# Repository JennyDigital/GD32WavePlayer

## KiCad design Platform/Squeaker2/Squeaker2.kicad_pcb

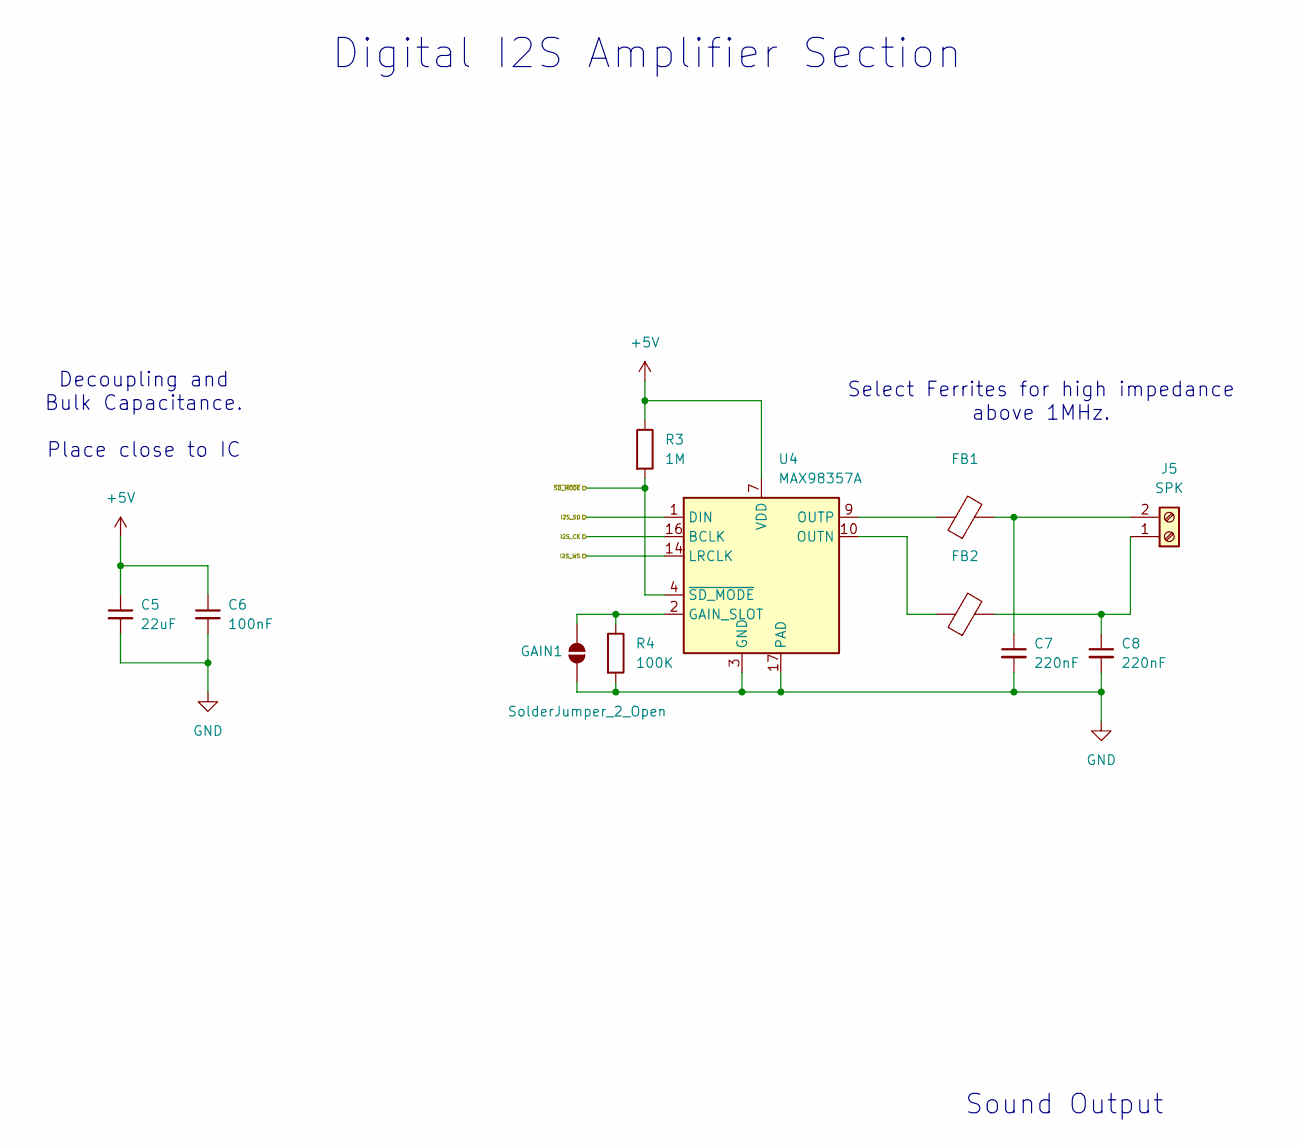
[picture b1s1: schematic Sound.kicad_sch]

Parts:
C5: 22uF; C_0603_1608Metric
C6: 100nF; C_0603_1608Metric
C7, C8: 220nF; C_0603_1608Metric
FB1, FB2: FerriteBead; L_0603_1608Metric
GAIN1: SolderJumper_2_Open; SolderJumper-2_P1.3mm_Open_RoundedPad1.0x1.5mm
J5: SPK; TerminalBlock_MetzConnect_Type073_RT02602HBLU_1x02_P5.08mm_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
R3: 1M; R_0603_1608Metric
R4: 100K; R_0603_1608Metric
U4: MAX98357A; TQFN-16-1EP_3x3mm_P0.5mm_EP1.23x1.23mm

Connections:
+5V: C5.1, C6.1, R3.1, U4.7 (VDD), U4.8 (VDD); also elsewhere on the board
/Processor/I2S_CK: U4.16 (BCLK); also elsewhere on the board
/Processor/I2S_SD: U4.1 (DIN); also elsewhere on the board
/Processor/I2S_WS: U4.14 (LRCLK); also elsewhere on the board
/Processor/~SD_MODE: R3.2, U4.4 (~SD_MODE); also elsewhere on the board
GND: C5.2, C6.2, C7.2, C8.2, GAIN1.1 (A), R4.2, U4.3 (GND), U4.11 (GND), U4.15 (GND), U4.17 (PAD); also elsewhere on the board
unnamed: GAIN1.2 (B), R4.1, U4.2 (GAIN_SLOT)
unnamed: C8.1, FB2.2, J5.1
unnamed: C7.1, FB1.2, J5.2
unnamed: FB2.1, U4.10 (OUTN)
unnamed: FB1.1, U4.9 (OUTP)

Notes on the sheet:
Sound Output
Select Ferrites for high impedance above 1MHz.
Digital I2S Amplifier Section
Decoupling and Bulk Capacitance. Place close to IC

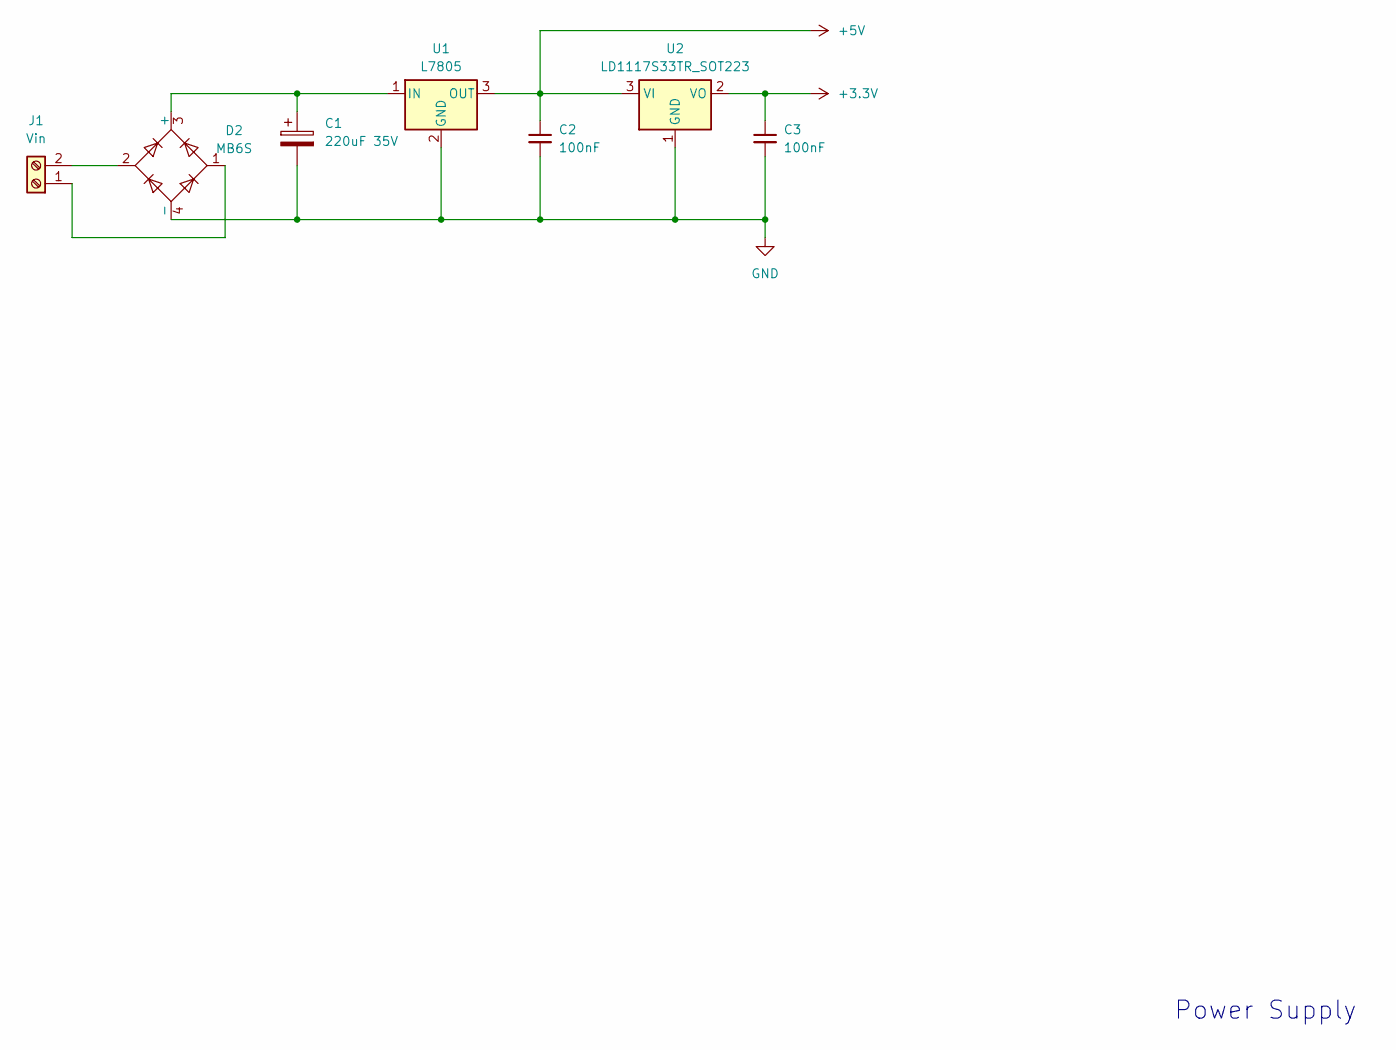
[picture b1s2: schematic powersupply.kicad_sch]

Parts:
C1: 220uF 35V; CP_Elec_8x10.5
C2, C3: 100nF; C_0603_1608Metric
D2: MB6S; TO-269AA
J1: Vin; TerminalBlock_MetzConnect_Type073_RT02602HBLU_1x02_P5.08mm_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
U1: L7805; TO-263-2
U2: LD1117S33TR_SOT223; SOT-223-3_TabPin2

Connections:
+3.3V: C3.1, U2.2 (VO); also elsewhere on the board
+5V: C2.1, U1.3 (OUT), U2.3 (VI); also elsewhere on the board
GND: C1.2, C2.2, C3.2, D2.4 (-), U1.2 (GND), U2.1 (GND); also elsewhere on the board
unnamed: C1.1, D2.3 (+), U1.1 (IN)
unnamed: D2.1, J1.1
unnamed: D2.2, J1.2

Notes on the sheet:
Power Supply

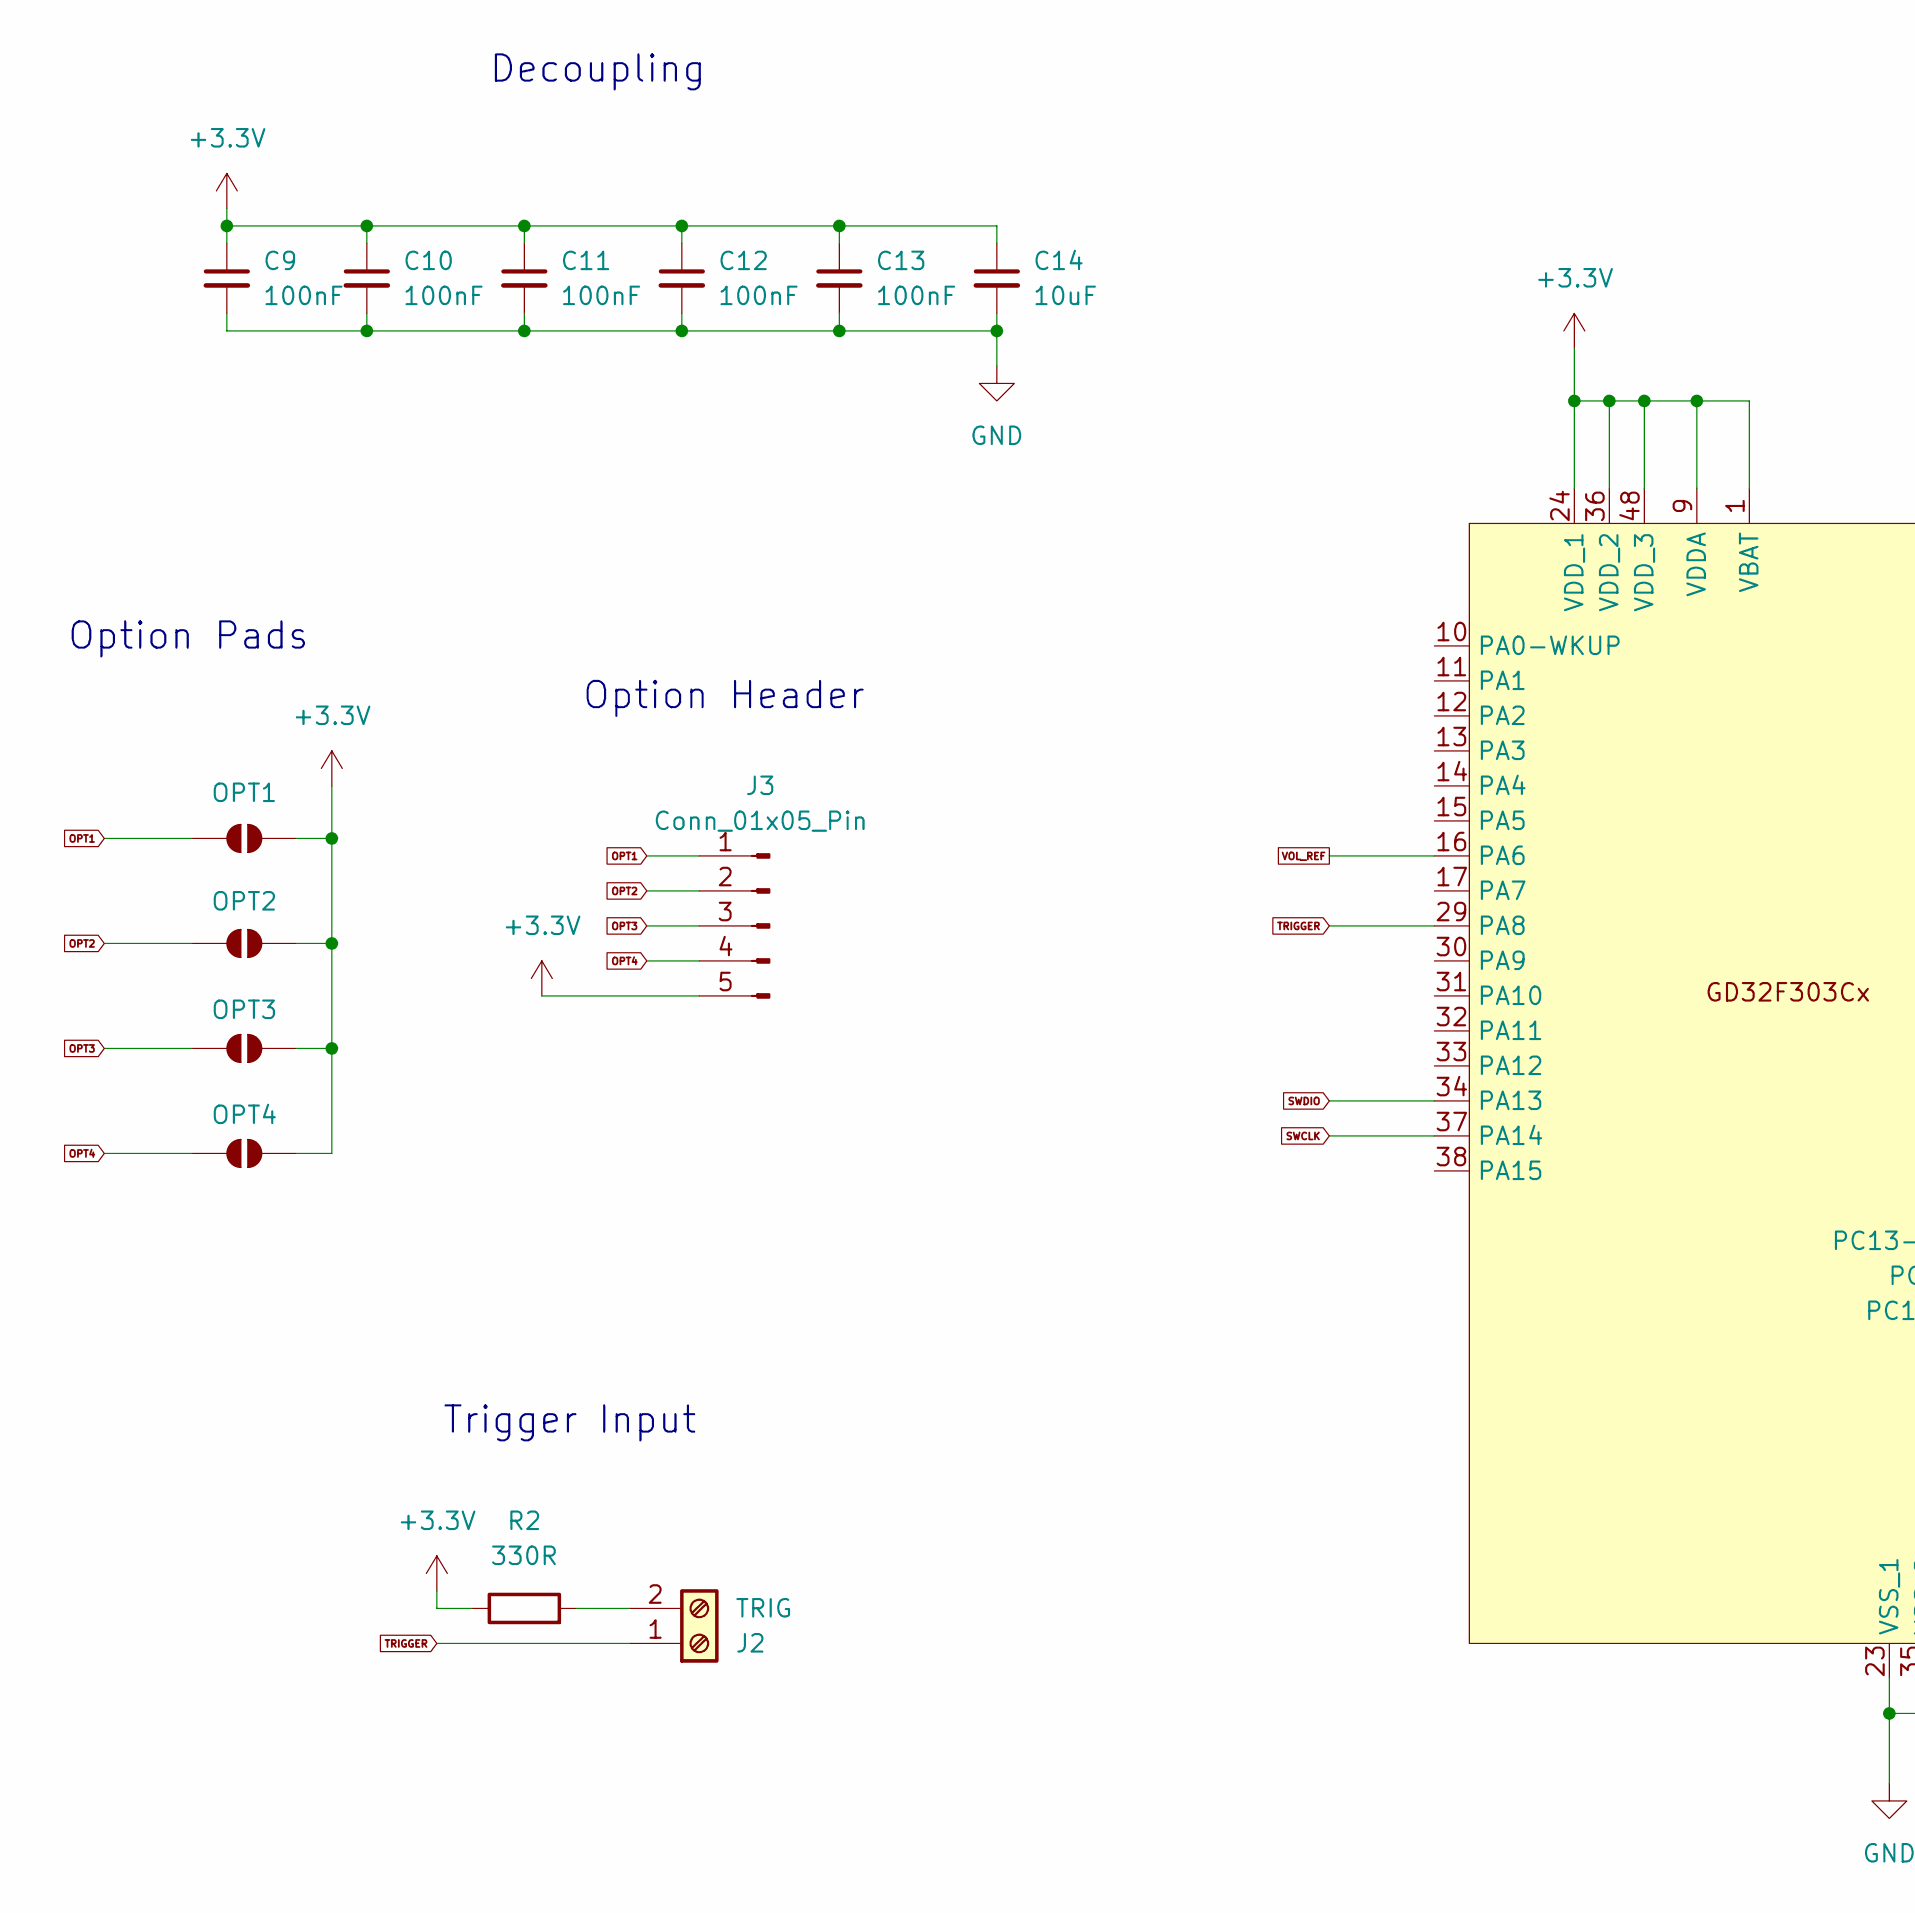
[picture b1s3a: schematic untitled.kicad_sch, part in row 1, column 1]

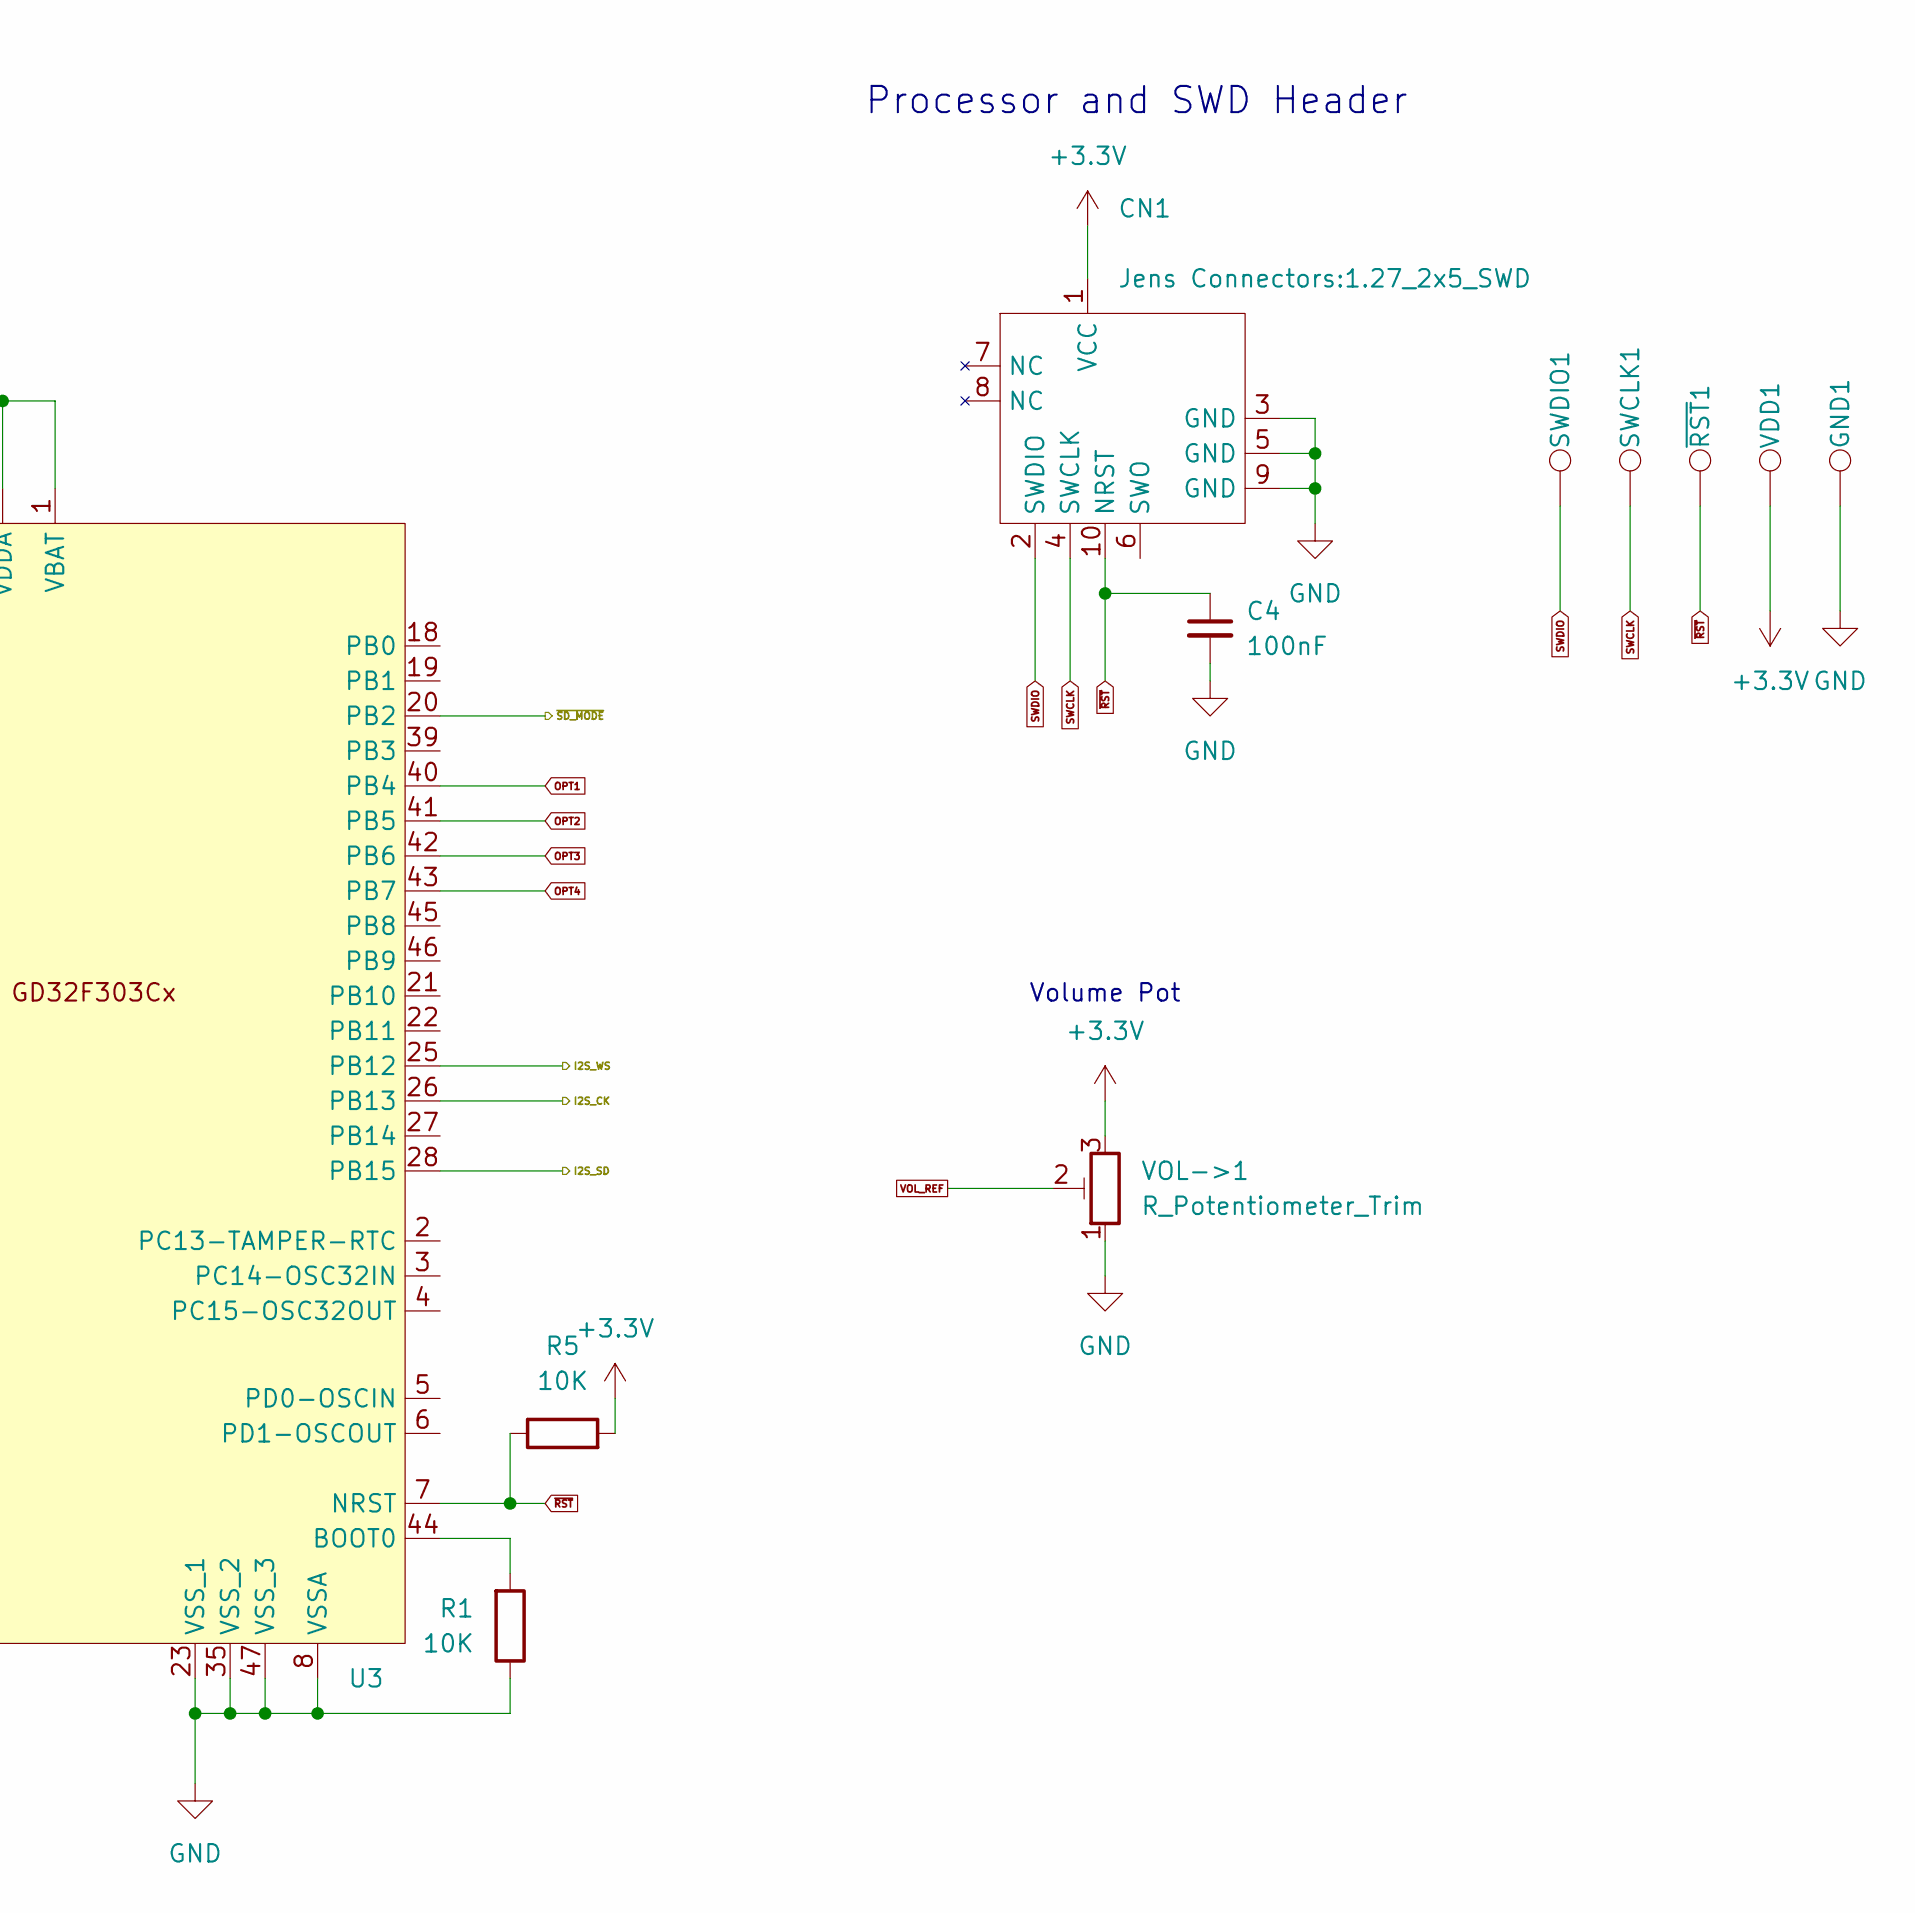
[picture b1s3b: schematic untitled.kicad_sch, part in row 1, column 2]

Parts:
C4, C9, C10, C11, C12, C13: 100nF; C_0603_1608Metric
C14: 10uF; C_0603_1608Metric
CN1: 1.27_2x5_SWD
GND1: TestPoint; TestPoint_Pad_D2.0mm
J2: TRIG; TerminalBlock_MetzConnect_Type073_RT02602HBLU_1x02_P5.08mm_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
J3: Conn_01x05_Pin; PinHeader_1x05_P2.54mm_Vertical
OPT1, OPT2, OPT3, OPT4: SolderJumper-2_P1.3mm_Open_RoundedPad1.0x1.5mm
R1, R5: 10K; R_0603_1608Metric
R2: 330R; R_0603_1608Metric
SWCLK1: TestPoint; TestPoint_Pad_D2.0mm
SWDIO1: TestPoint; TestPoint_Pad_D2.0mm
U3: TQFP-48_7x7mm_P0.5mm
VDD1: TestPoint; TestPoint_Pad_D2.0mm
VOL->1: R_Potentiometer_Trim; BOURNS-3362P_pot
~{RST}1: TestPoint; TestPoint_Pad_D2.0mm

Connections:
+3.3V: C9.1, C10.1, C11.1, C12.1, C13.1, C14.1, CN1.1 (VCC), J3.5, OPT1.2 (B), OPT2.2 (B), OPT3.2 (B), OPT4.2 (B), R2.1, R5.2, U3.1 (VBAT), U3.9 (VDDA), U3.24 (VDD_1), U3.36 (VDD_2), U3.48 (VDD_3), VDD1.1, VOL->1.3; also elsewhere on the board
/Processor/I2S_CK: U3.26 (PB13); also elsewhere on the board
/Processor/I2S_SD: U3.28 (PB15); also elsewhere on the board
/Processor/I2S_WS: U3.25 (PB12); also elsewhere on the board
/Processor/~SD_MODE: U3.20 (PB2); also elsewhere on the board
GND: C4.2, C9.2, C10.2, C11.2, C12.2, C13.2, C14.2, CN1.3 (GND), CN1.5 (GND), CN1.9 (GND), GND1.1, R1.1, U3.8 (VSSA), U3.23 (VSS_1), U3.35 (VSS_2), U3.47 (VSS_3), VOL->1.1; also elsewhere on the board
unnamed: J2.2, R2.2
unnamed: R1.2, U3.44 (BOOT0)
OPT1: J3.1, OPT1.1 (A), U3.40 (PB4)
OPT2: J3.2, OPT2.1 (A), U3.41 (PB5)
OPT3: J3.3, OPT3.1 (A), U3.42 (PB6)
OPT4: J3.4, OPT4.1 (A), U3.43 (PB7)
SWCLK: CN1.4 (SWCLK), SWCLK1.1, U3.37 (PA14)
SWDIO: CN1.2 (SWDIO), SWDIO1.1, U3.34 (PA13)
TRIGGER: J2.1, U3.29 (PA8)
VOL_REF: U3.16 (PA6), VOL->1.2; also elsewhere on the board
~RST: C4.1, CN1.10 (NRST), R5.1, U3.7 (NRST), ~{RST}1.1

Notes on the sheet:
Option Header
Decoupling
Processor and SWD Header
Trigger Input
Volume Pot
Option Pads

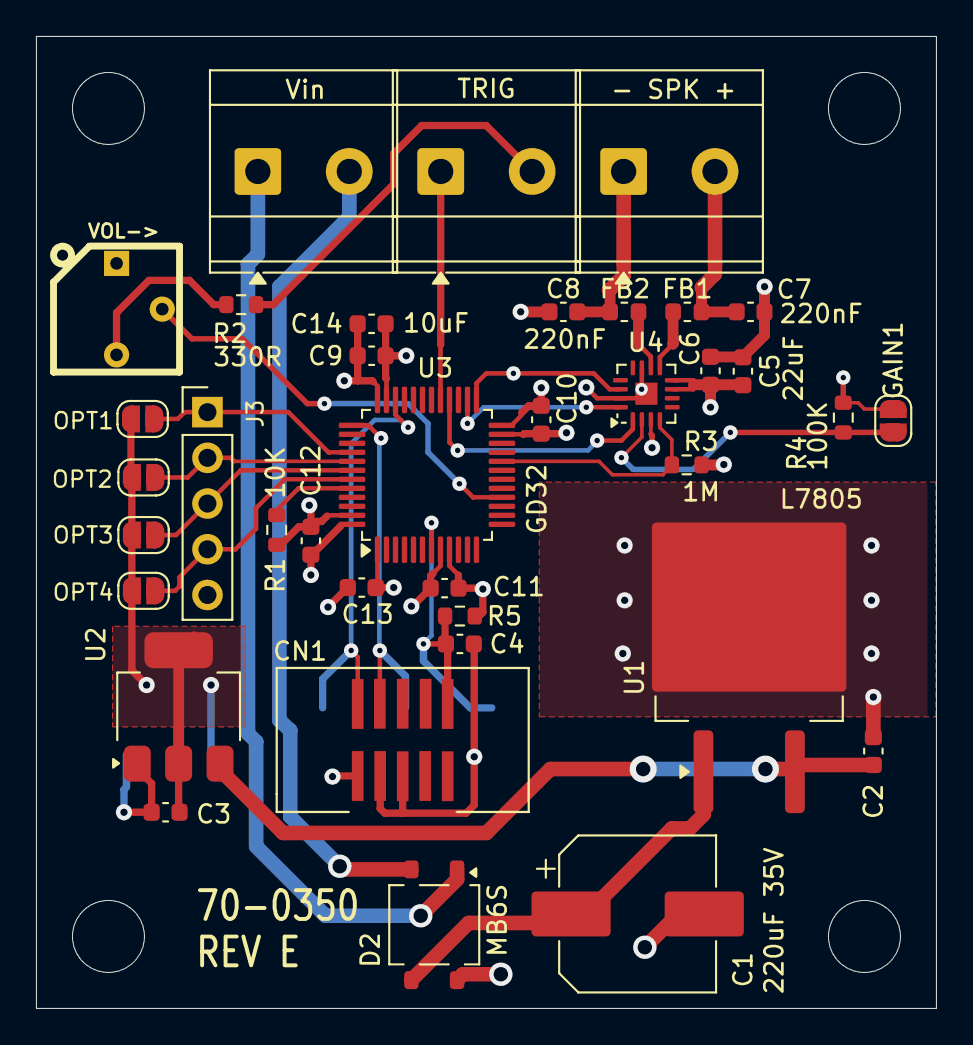
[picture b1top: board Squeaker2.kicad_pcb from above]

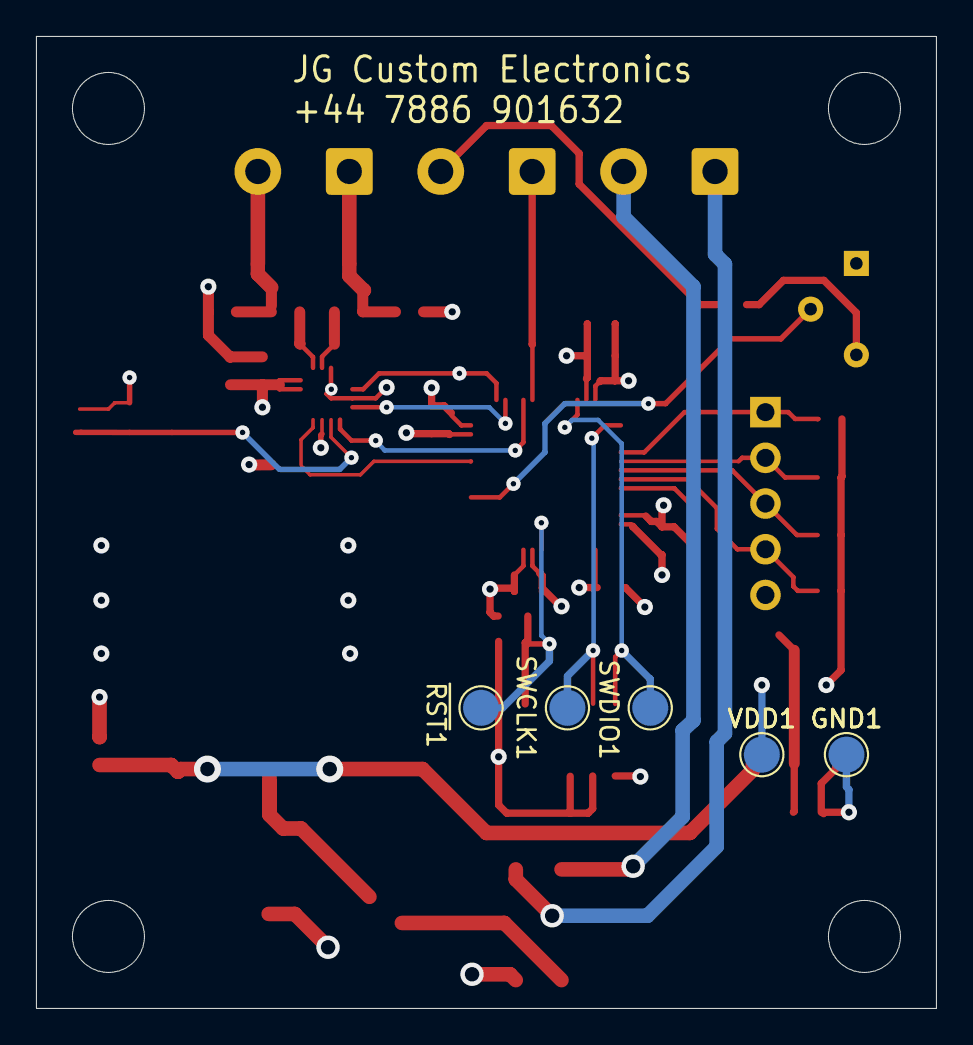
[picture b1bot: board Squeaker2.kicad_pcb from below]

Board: 4 copper layers, 50.0 x 54.0 mm, 41 parts (4 on the bottom side), 26 nets.

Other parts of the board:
VOL->: R_Potentiometer_Trim; BOURNS-3362P_pot

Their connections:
+3.3V: VOL->.3; also elsewhere on the board
GND: VOL->.1; also elsewhere on the board
VOL_REF: VOL->.2; also elsewhere on the board

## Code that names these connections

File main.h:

#ifndef _MAIN_H
#define _MAIN_H

/** Pin definitions
  *
  */

  // Option Pins
  //
  #define OPT1_Pin            GPIO_PIN_4
  #define OPT1_Bank           GPIOB
  #define OPT2_Pin            GPIO_PIN_5
  #define OPT2_Bank           GPIOB
  #define OPT3_Pin            GPIO_PIN_6
  #define OPT3_Bank           GPIOB
  #define OPT4_Pin            GPIO_PIN_7
  #define OPT4_Bank           GPIOB

  // Trigger Pin
  //
  #define TRIGGER_Pin         GPIO_PIN_8
  #define TRIGGER_Bank        GPIOA

  // I2S Support Pins
  //
  #define nSD_MODE_Pin        GPIO_PIN_2
  #define nSD_MODE_BANK       GPIOB
  #define I2S_WS_Pin          GPIO_PIN_12
  #define I2S_WS_BANK         GPIOB
  #define I2S_CK_Pin          GPIO_PIN_13
  #define I2S_CK_BANK         GPIOB
  #define I2S_SD_Pin          GPIO_PIN_15
  #define I2S_SD_BANK         GPIOB

  // ADC Input Pin
  //
  #define VOLRef_Pin          GPIO_PIN_6
  #define VOLRef_BANK         GPIOA

  // Defines for I2S
  //
  #define PROJECT_SPI         SPI1        // The port used on the PCB design, no remap is available.
  #define PROJECT_SPI_CLOCK   RCU_SPI1    // Clock for above peripheral.


// Trigger counter values
#define TC_LOW_THRESHOLD      60U
#define TC_HIGH_THRESHOLD     120U
#define TC_MAX                240U
#define TRIGGER_SET           1
#define TRIGGER_CLR           0
#define TRIG_TIMEOUT_MS       1000U

// Analog volume ADC scaling (12-bit ADC scaled to 16-bit range)
// ADC max (4095) * 16 = 65520, representing the maximum usable 16-bit volume value
#define VOLUME_ADC_MAX_SCALED 65520U

// Scale factor for master volume input.
#define MASTER_VOLUME_SCALE 8U

// Volume floor value
#define MASTER_VOLUME_MINIMUM 8U

// Sleep mode control. Comment out for sleep feature.
//#define NO_SLEEP_MODE

/* Build options */ 
#define FORCE_TRIGGER_OPT
//#define TEST_CYCLING
//#define DALBY_BUILD

  // Includes
  //
  #include <gd32f30x.h>

#endif // _MAIN_H

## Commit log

2026-02-13 FEATURE:- Now sporting sleep mode when idle. TIDY:- Removed some dead code and unused variables.
2026-02-14 FIX: Integer overflow in ComputeSoftClipCurve function.
2026-02-14 Upped the running speed to 120MHz, as fast as possible.
2026-02-14 Missed a few files
2026-02-14 Added a macro (PUT_IN_FASTMEM) that applies the following attribute: __attribute__((section(".fast"))) This ensures that speed is optimized.
2026-02-14 FEATURE: Added ADC volume input on PA6.
2026-02-14 FEATURE:- ADC Volume signal is now filtered.
2026-02-15 FIX: ADC1 regular channel wasn't mapped to PA6! Volume now works as it should.
2026-02-15 Removed redundant code from audio_engine.c
2026-02-15 Improved conditional compilation of GetTriggerOption
2026-02-22 FIX: Fadeout now behaves more smoothly, accounting for samples, mnot just half-buffers
2026-02-23 Dalby multi-feature build
2026-02-23 Changed the three tone chime sound to the better one.
2026-02-24 Removed digital volume option.
2026-02-25 IMPROVEMENT
    Minor tweaks.
2026-02-26 Added new functionality and consistency to the dalby mode
2026-02-27 FIX: AudioEngine_OnEndOfPlay wasn't triggering at normal end. FIX: Chime did not respond for one whole cycle to mode change.
2026-02-27 FIX: Revert forgotten test configuration lines
2026-02-28 FIX: The adjusted volume setting is now only recalculated if the incoming volume setting has changed.
2026-03-01 Updated to latest revision of the audio engine with ports from the STM32 version
2026-03-01 Upgraded volume handling to per frame rather than per chunk. FIX: SPI DMA wasn't being stopped with the correct parameter.
2026-03-01 ADD: Documentation from the STM32 version amended and added.
2026-03-02 FIX: When OPT_DoorsOpeningClosing was selected, it would get trapped in this mode. conditional breaks added to solve this.
2026-03-03 FEATURE: Added chime no trigger mode.
2026-03-04 Tweaks to dalby_multi operation
2026-03-06 Added better managed sound for Dalby TT chime
2026-03-06 Checkpoint before making a significant structural change.
2026-03-06 FIX: Playback state is now properly and explicitly reset at playback start.
2026-03-08 ADD: New sound FIX: Having fixed the DAC switching feature, it became apparent that the Systick handler was being blocked. Priorities now adjusted.
2026-03-10 FIX: Removed the audio engine's dependency on interrupts, allowing it to be used in a wider range of applications and environments. This prevents SysTick interrupt blocking from locking up the audio 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
2026-03-16 Fixed triggering issues It will now build in vscode. I still won't debug in vscode.
2026-03-17 Update to WaitForTrigger.
2026-03-17 Missed main.h!
2026-03-19 UPDATE Library for parity with the STM32 version.
2026-03-25 TIDY: main.c, edited the comments to be more consistent and clear. No code changes, just comment formatting and wording.
2026-03-31 Add platform and gerber files.
2026-04-03 Monor formatting adjustments, no functional changes
2026-05-02 FEATURE: Added ADPCM decode support.
2026-05-27 Just a small addition
